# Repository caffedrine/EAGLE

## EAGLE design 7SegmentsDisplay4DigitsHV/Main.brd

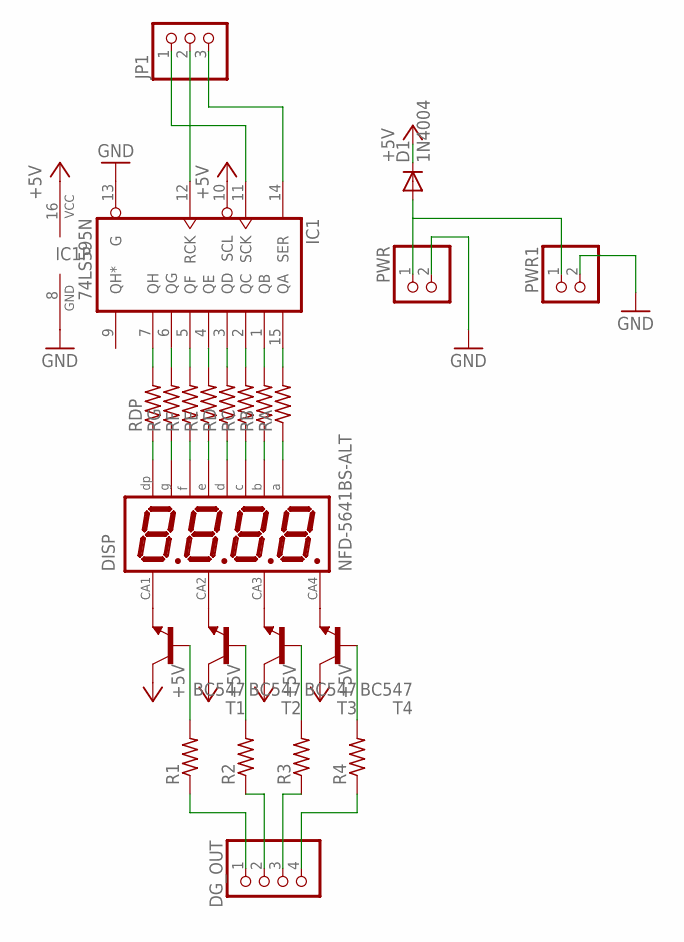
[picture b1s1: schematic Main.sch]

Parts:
D1: 1N4004; DO41-10
DG_OUT: PINHD-1X4; 1X04
DISP: NFD-5641BS-ALT; NFD-5641
IC1: 74LS595N; DIL16
JP1: PINHD-1X3; 1X03
PWR, PWR1: PINHD-1X2; 1X02
R1, R2, R3, R4: R-US_0309/12; 0309/12
RA: R-US_0309/12; 0309/12
RB: R-US_0309/12; 0309/12
RC: R-US_0309/12; 0309/12
RD: R-US_0309/12; 0309/12
RDP: R-US_0309/12; 0309/12
RE: R-US_0309/12; 0309/12
RF: R-US_0309/12; 0309/12
RG: R-US_0309/12; 0309/12
T1, T2, T3, T4: BC547; TO92

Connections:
+5V: D1.C, IC1.10 (SCL), IC1.16 (VCC), T1.3 (C), T2.3 (C), T3.3 (C), T4.3 (C)
GND: IC1.8 (GND), IC1.13 (G), PWR.2, PWR1.2
unnamed: DISP.P$12, T1.1 (E)
unnamed: DISP.P$9, T2.1 (E)
unnamed: DISP.P$8, T3.1 (E)
unnamed: DISP.P$6, T4.1 (E)
unnamed: R1.2, T1.2 (B)
unnamed: R2.2, T2.2 (B)
unnamed: R3.2, T3.2 (B)
unnamed: R4.2, T4.2 (B)
unnamed: DG_OUT.2, R2.1
unnamed: DG_OUT.3, R3.1
unnamed: DG_OUT.4, R4.1
unnamed: DG_OUT.1, R1.1
unnamed: IC1.7 (QH), RDP.2
unnamed: IC1.6 (QG), RG.2
unnamed: IC1.5 (QF), RF.2
unnamed: IC1.4 (QE), RE.2
unnamed: IC1.3 (QD), RD.2
unnamed: IC1.2 (QC), RC.2
unnamed: IC1.1 (QB), RB.2
unnamed: IC1.15 (QA), RA.2
unnamed: IC1.11 (SCK), JP1.1
unnamed: IC1.12 (RCK), JP1.2
unnamed: IC1.14 (SER), JP1.3
unnamed: DISP.P$3, RDP.1
unnamed: DISP.P$5, RG.1
unnamed: DISP.P$10, RF.1
unnamed: DISP.P$1, RE.1
unnamed: DISP.P$2, RD.1
unnamed: DISP.P$4, RC.1
unnamed: DISP.P$7, RB.1
unnamed: DISP.P$11, RA.1
unnamed: D1.A, PWR.1, PWR1.1

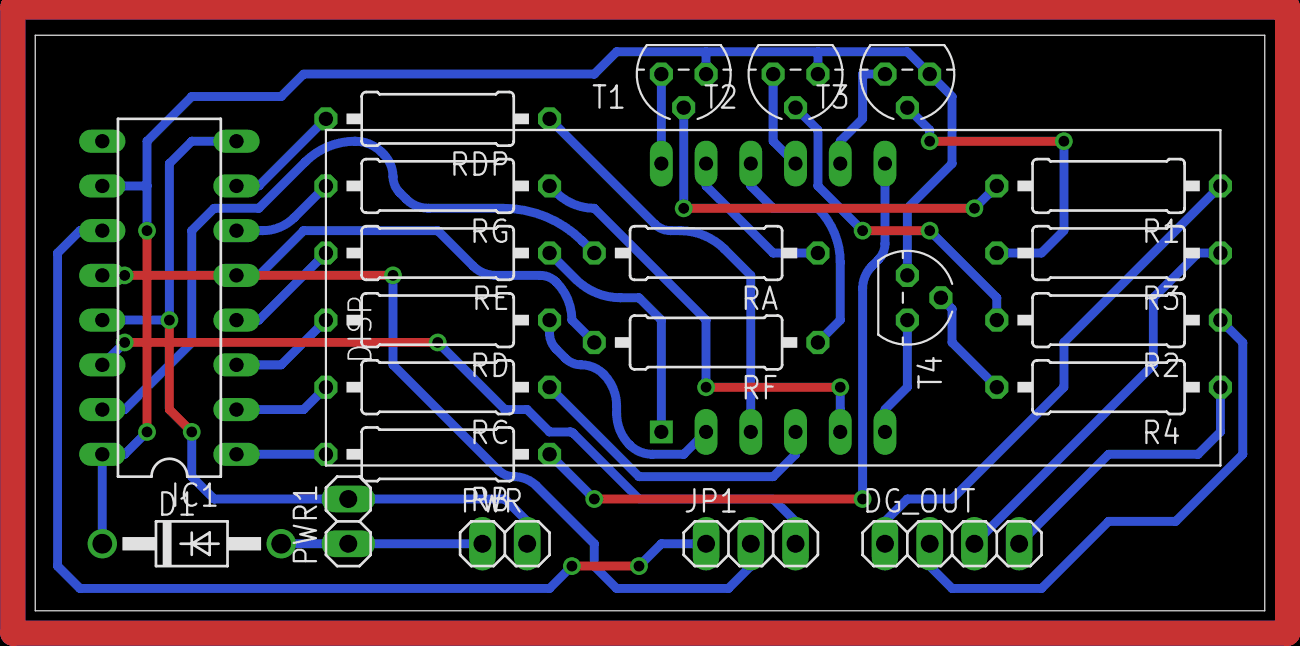
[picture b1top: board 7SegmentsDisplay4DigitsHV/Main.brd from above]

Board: 3 copper layers, 69.8 x 32.7 mm, 23 parts (0 on the bottom side), 34 nets.

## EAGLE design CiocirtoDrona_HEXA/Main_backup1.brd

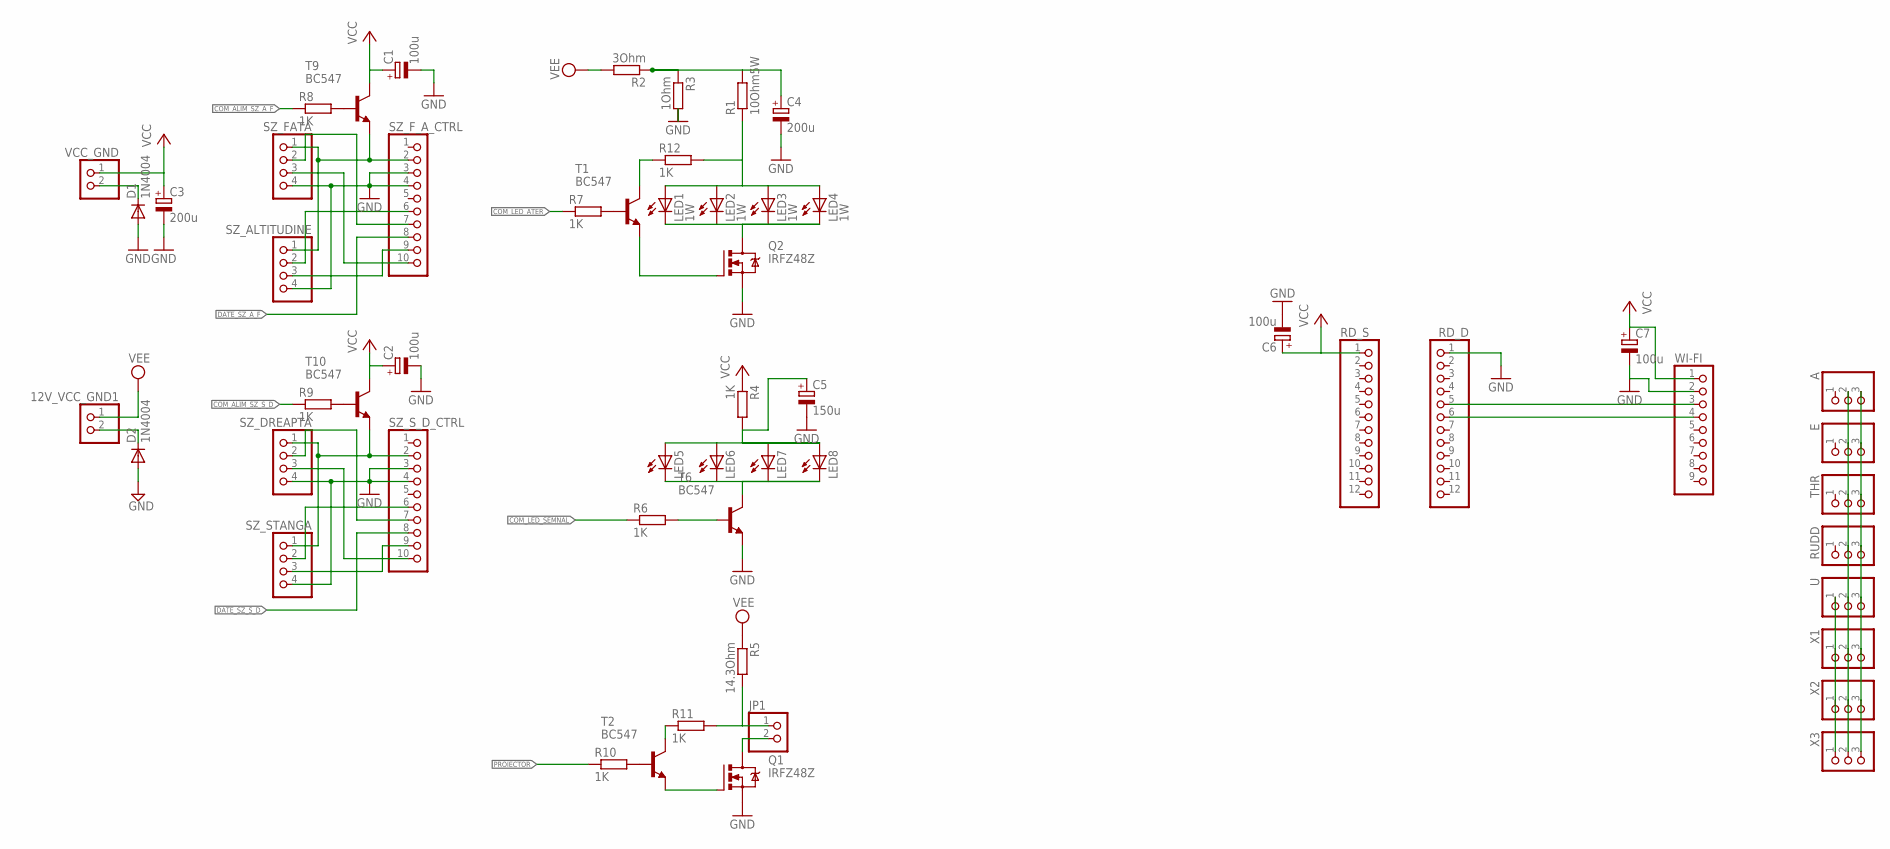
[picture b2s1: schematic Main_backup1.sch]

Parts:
12V_VCC_GND1: PINHD-1X2; 1X02
A: PINHD-1X3/90; 1X03/90
C1, C2, C6, C7: 100u; E2-5
C3, C4: 200u; E2-5
C5: 150u; E2-5
D1, D2: 1N4004; DO41-10
E: PINHD-1X3/90; 1X03/90
JP1: PINHD-1X2; 1X02
LED1, LED2, LED3, LED4: 1W; OSRAM-SIDELED
LED5, LED6, LED7, LED8: LED5MM
Q1, Q2: IRFZ48Z; TO220BH
R1: 10Ohm5W; 0309/12
R2: 3Ohm; 0309/12
R3: 1Ohm; 0309/12
R4, R6, R7, R8, R9, R10, R11, R12: 1K; 0309/12
R5: 14.3Ohm; 0309/12
RD_D: PINHD-1X12; 1X12
RD_S: PINHD-1X12; 1X12
RUDD: PINHD-1X3/90; 1X03/90
SZ_ALTITUDINE: PINHD-1X4; 1X04
SZ_DREAPTA: PINHD-1X4; 1X04
SZ_FATA: PINHD-1X4; 1X04
SZ_F_A_CTRL: PINHD-1X10; 1X10
SZ_STANGA: PINHD-1X4; 1X04
SZ_S_D_CTRL: PINHD-1X10; 1X10
T1, T2, T6, T9, T10: BC547; TO92
THR: PINHD-1X3/90; 1X03/90
U: PINHD-1X3/90; 1X03/90
VCC_GND: PINHD-1X2; 1X02
WI-FI: PINHD-1X9; 1X09
X1, X2, X3: PINHD-1X3/90; 1X03/90

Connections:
COM_ALIM_SZ_A_F: R8.1
COM_ALIM_SZ_S_D: R9.1
COM_LED_ATER: R7.1
COM_LED_SEMNAL: R6.1
DATE_SZ_A_F: SZ_F_A_CTRL.8
DATE_SZ_S_D: SZ_S_D_CTRL.8
GND: C1.-, C2.-, C3.-, C4.-, C5.-, C6.-, C7.-, D1.A, D2.A, Q1.S, Q2.S, R3.2, RD_D.1, SZ_ALTITUDINE.4, SZ_DREAPTA.4, SZ_FATA.4, SZ_F_A_CTRL.3, SZ_F_A_CTRL.4, SZ_STANGA.4, SZ_S_D_CTRL.3, SZ_S_D_CTRL.4, T6.1 (E), WI-FI.2
unnamed: SZ_FATA.2, SZ_F_A_CTRL.7
unnamed: D1.C, VCC_GND.2
unnamed: JP1.1, R5.2, R11.2
unnamed: SZ_FATA.3, SZ_F_A_CTRL.10
unnamed: SZ_ALTITUDINE.2, SZ_F_A_CTRL.6
unnamed: SZ_ALTITUDINE.3, SZ_F_A_CTRL.9
unnamed: SZ_DREAPTA.2, SZ_S_D_CTRL.7
unnamed: SZ_DREAPTA.3, SZ_S_D_CTRL.10
unnamed: SZ_STANGA.2, SZ_S_D_CTRL.6
unnamed: SZ_STANGA.3, SZ_S_D_CTRL.9
unnamed: SZ_ALTITUDINE.1, SZ_FATA.1, SZ_F_A_CTRL.2, T9.1 (E)
unnamed: SZ_DREAPTA.1, SZ_STANGA.1, SZ_S_D_CTRL.2, T10.1 (E)
unnamed: LED1.C, LED2.C, LED3.C, LED4.C, Q2.D
unnamed: LED1.A, LED2.A, LED3.A, LED4.A, R1.1, R12.2
unnamed: Q2.G, T1.1 (E)
unnamed: C4.+, R1.2, R2.1, R3.1
unnamed: 12V_VCC_GND1.2, D2.C
unnamed: LED5.K (C), LED6.K (C), LED7.K (C), LED8.K (C), T6.3 (C)
unnamed: C5.+, LED5.A, LED6.A, LED7.A, LED8.A, R4.2
unnamed: JP1.2, Q1.D
unnamed: R6.2, T6.2 (B)
unnamed: R7.2, T1.2 (B)
unnamed: R8.2, T9.2 (B)
unnamed: R9.2, T10.2 (B)
unnamed: R10.2, T2.2 (B)
unnamed: R12.1, T1.3 (C)
unnamed: R11.1, T2.3 (C)
unnamed: Q1.G, T2.1 (E)
unnamed: U.1, X1.1, X2.1, X3.1
unnamed: RD_D.5, WI-FI.3
unnamed: RD_D.6, WI-FI.4
unnamed: A.3, E.3, RUDD.3, THR.3, U.3, X1.3, X2.3, X3.3
unnamed: A.2, E.2, RUDD.2, THR.2, U.2, X1.2, X2.2, X3.2
PROIECTOR: R10.1
VCC: C1.+, C2.+, C3.+, C6.+, C7.+, R4.1, RD_S.1, T9.3 (C), T10.3 (C), VCC_GND.1, WI-FI.1
VEE: 12V_VCC_GND1.1, R2.2, R5.1

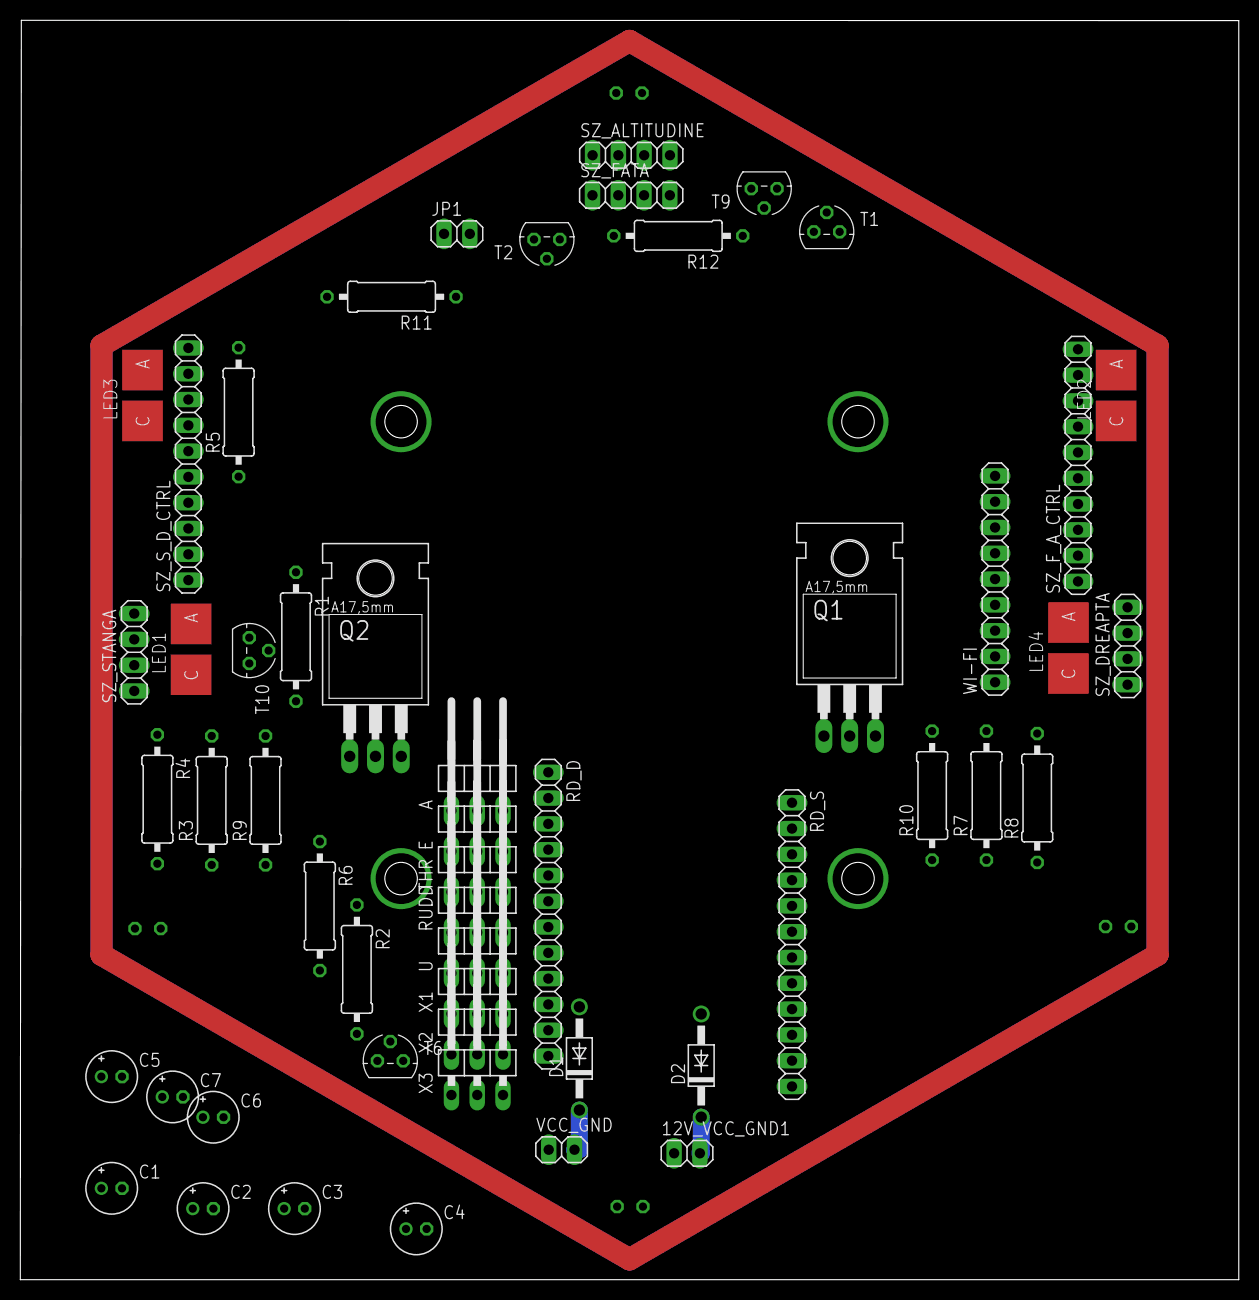
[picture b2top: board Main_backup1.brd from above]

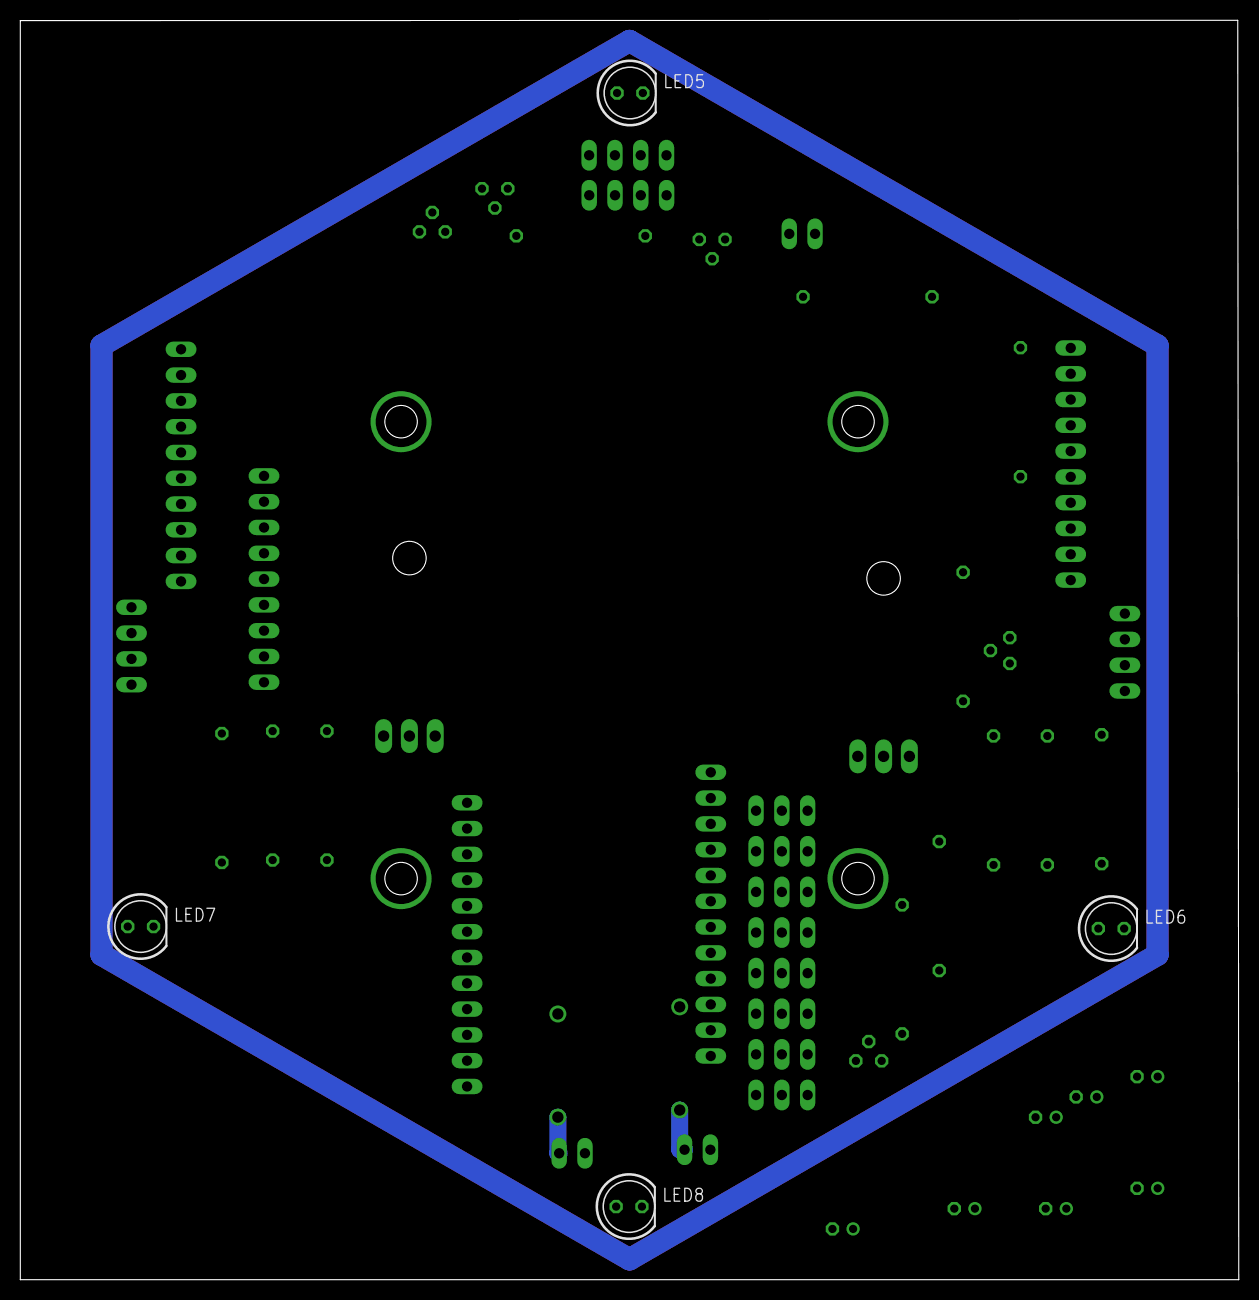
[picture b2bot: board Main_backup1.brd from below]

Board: 2 copper layers, 120.0 x 124.0 mm, 56 parts (4 on the bottom side), 36 nets.

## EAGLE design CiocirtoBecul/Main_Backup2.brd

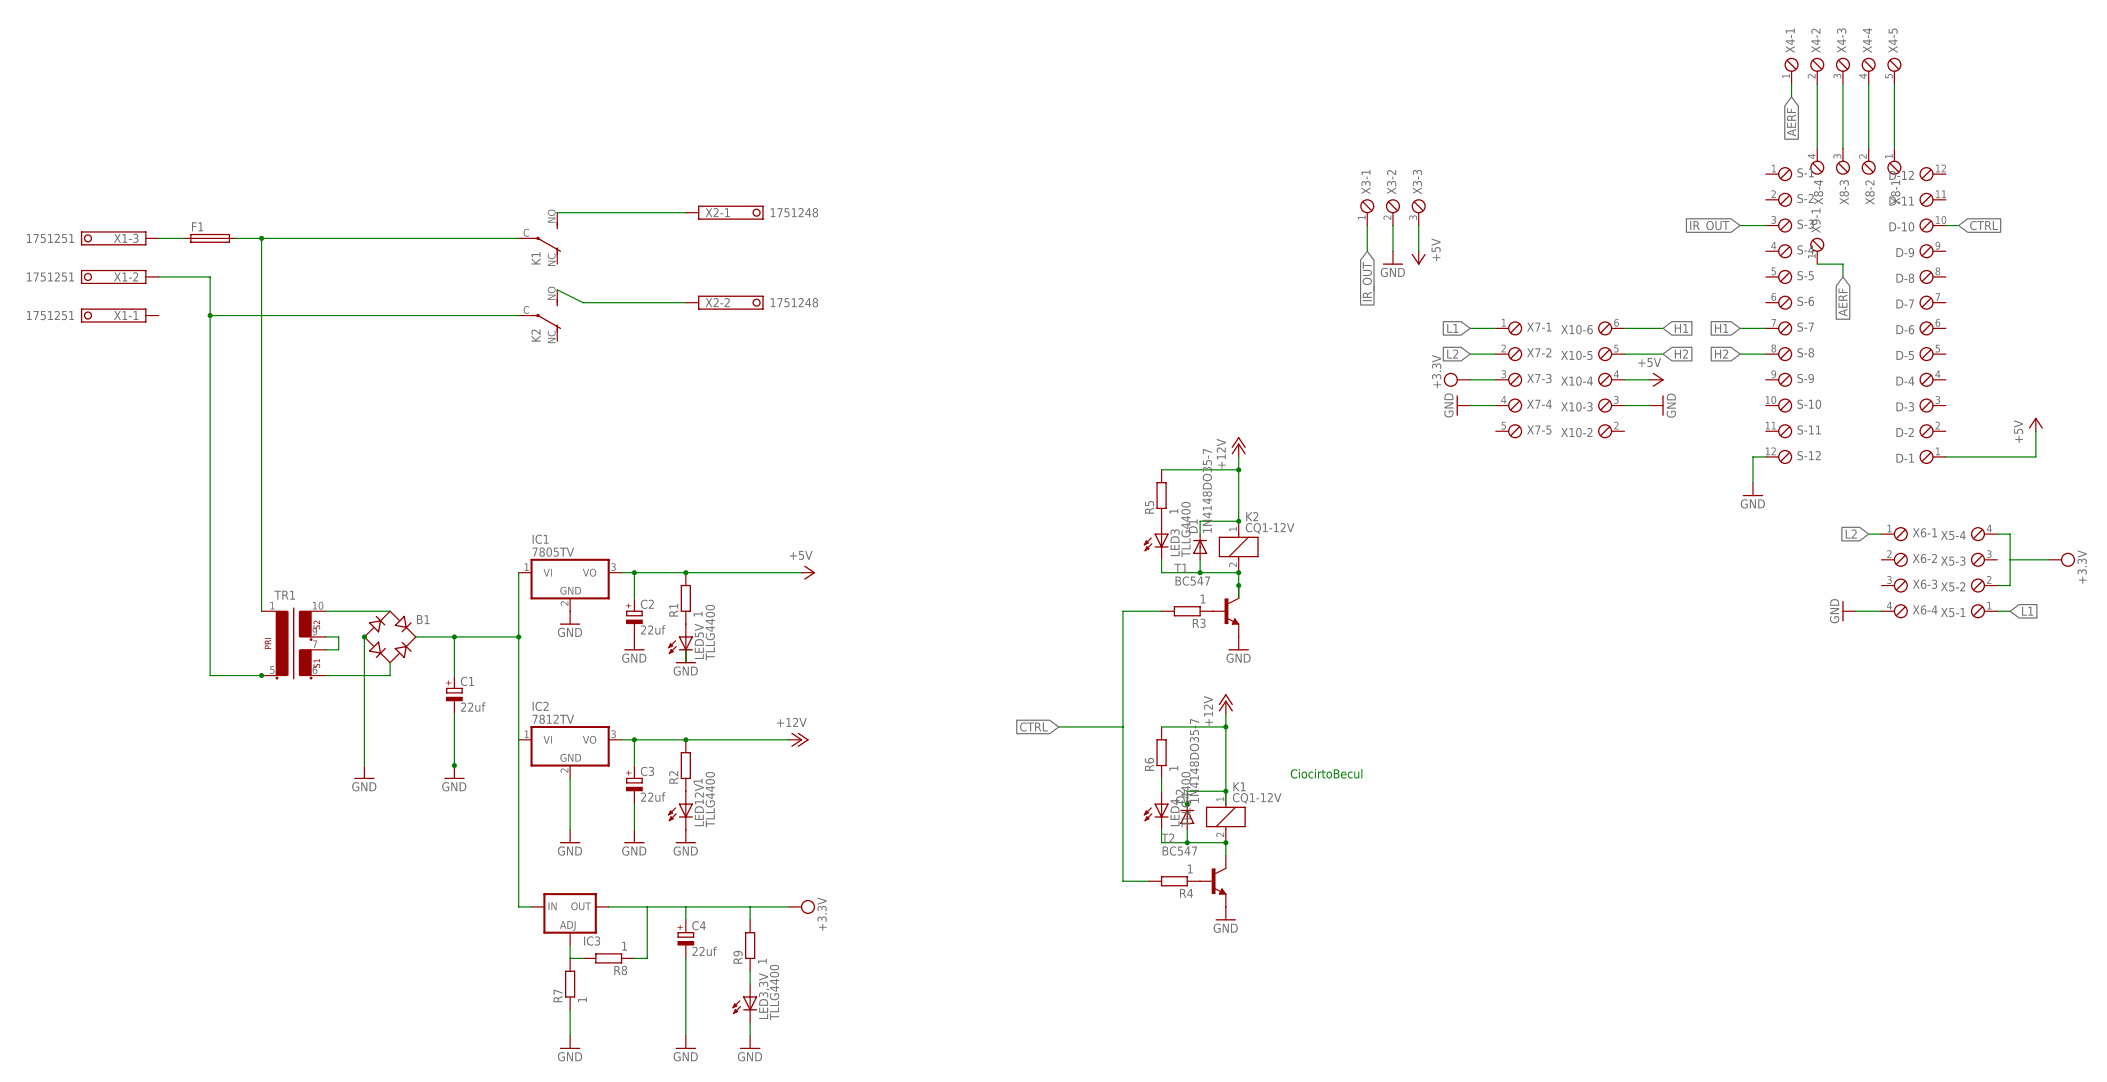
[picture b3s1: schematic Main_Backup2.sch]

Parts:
B1: RB1A
C1, C2, C3, C4: 22uf; E2-4
D: MPT12; 12POL254
D1, D2: 1N4148DO35-7; DO35-7
F1: SH25
IC1: 7805TV; TO220V
IC2: 7812TV; TO220V
IC3: LM317TS; 317TS
K1, K2: CQ1-12V; CQ1
LED3, LED3,3V, LED4, LED5V, LED12V: TLLG4400; LED3MM
R1, R2, R3, R4, R5, R6, R7, R8, R9: 1; 0204/5
S: MPT12; 12POL254
T1, T2: BC547; TO92
TR1: EI30-2
X1: 1751251
X2: 1751248
X3: MPT3; 3POL254
X4: MPT5; 5POL254
X5, X6, X8: MPT4; 4POL254
X7, X10: MPT6; 6POL254
X9: MPT2; 2POL254

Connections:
+5V: C2.+, D.1, IC1.3 (VO), R1.2, X3.3, X10.4
+12V: C3.+, D1.C, D2.C, IC2.3 (VO), K1.1, K2.1, R2.2, R5.2, R6.2
AERF: X4.1, X9.1
CTRL: D.10, R3.2, R4.2
GND: B1.-, C1.-, C2.-, C3.-, C4.-, IC1.2 (GND), IC2.2 (GND), LED3,3V.K (C), LED5V.K (C), LED12V.K (C), R7.1, S.12, T1.1 (E), T2.1 (E), X3.2, X6.4, X7.4, X10.3
H1: S.7, X10.6
H2: S.8, X10.5
IR_OUT: S.3, X3.1
L1: X5.1, X7.1
L2: X6.1, X7.2
unnamed: F1.2, K1.C, TR1.1
unnamed: K2.C, TR1.5 (2), X1.2
unnamed: K1.NO (S), X2.1
unnamed: K2.NO (S), X2.2
unnamed: TR1.7 (4), TR1.9 (5)
unnamed: B1.AC1, TR1.10 (6)
unnamed: B1.AC2, TR1.6 (3)
unnamed: B1.+, C1.+, IC1.1 (VI), IC2.1 (VI), IC3.3 (IN)
unnamed: D1.A, K2.2, LED3.K (C), T1.3 (C)
unnamed: LED12V.A, R2.1
unnamed: LED3.A, R5.1
unnamed: D2.A, K1.2, LED4.K (C), T2.3 (C)
unnamed: LED5V.A, R1.1
unnamed: R3.1, T1.2 (B)
unnamed: R4.1, T2.2 (B)
unnamed: X4.5, X8.1
unnamed: F1.1, X1.3
unnamed: LED4.A, R6.1
unnamed: IC3.1 (ADJ), R7.2, R8.2
unnamed: LED3,3V.A, R9.1
unnamed: X4.3, X8.3
unnamed: X4.4, X8.2
unnamed: X4.2, X8.4
VCC: C4.+, IC3.2 (OUT), R8.1, R9.2, X5.2, X5.4, X7.3

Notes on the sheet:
CiocirtoBecul

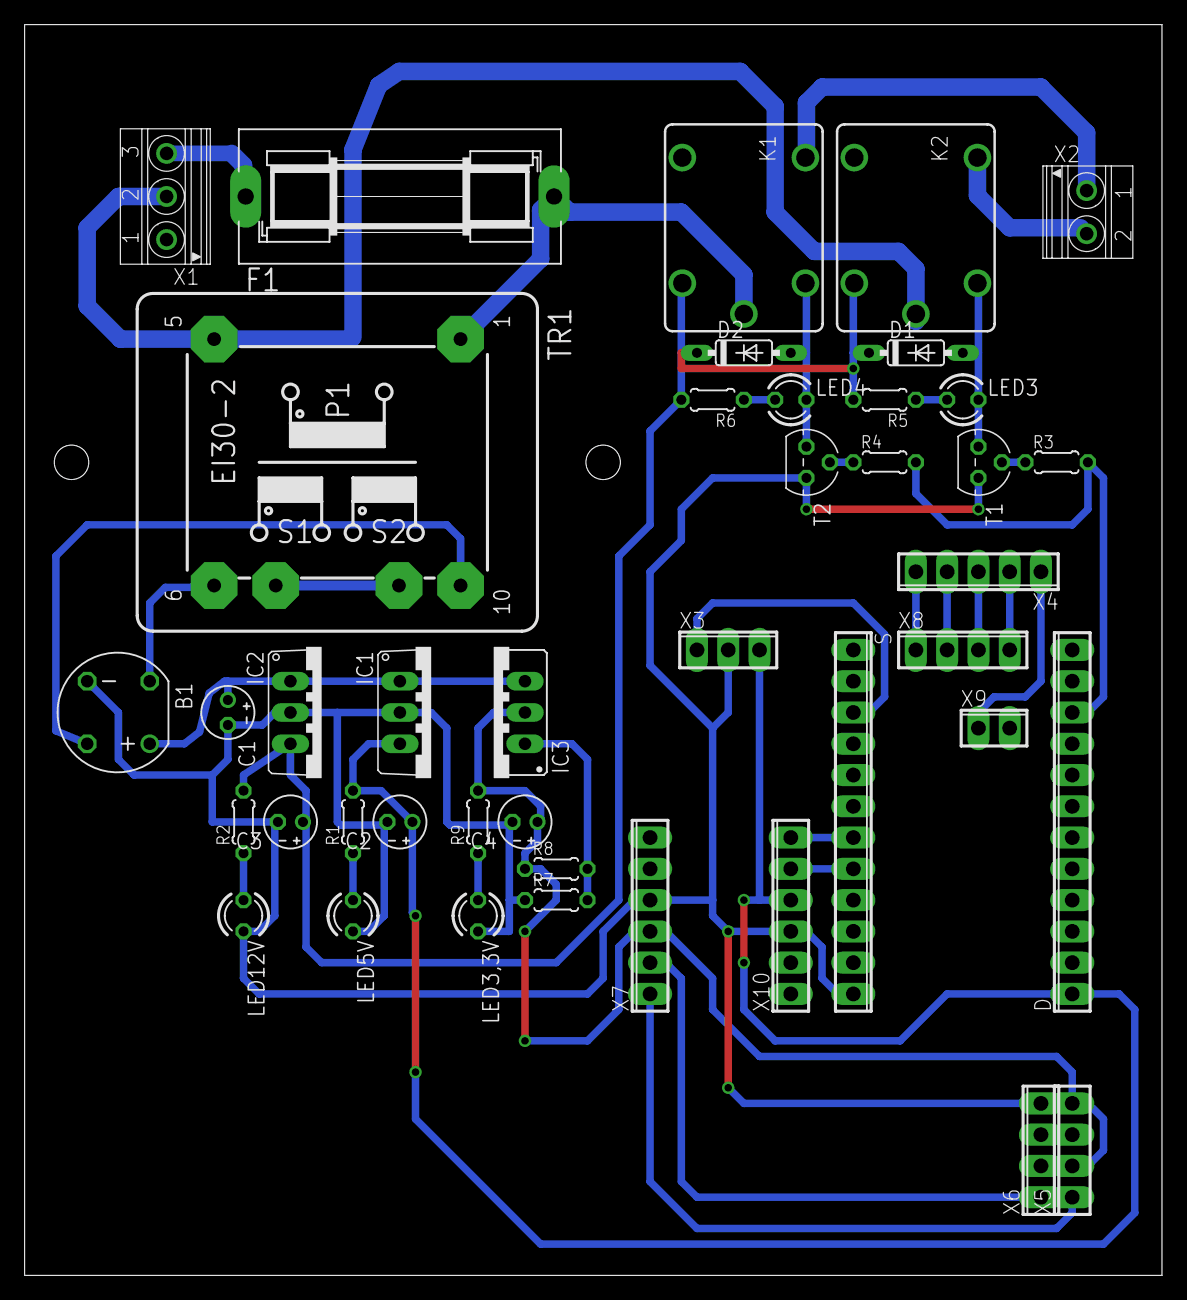
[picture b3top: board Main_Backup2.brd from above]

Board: 2 copper layers, 92.4 x 101.6 mm, 42 parts (0 on the bottom side), 34 nets.

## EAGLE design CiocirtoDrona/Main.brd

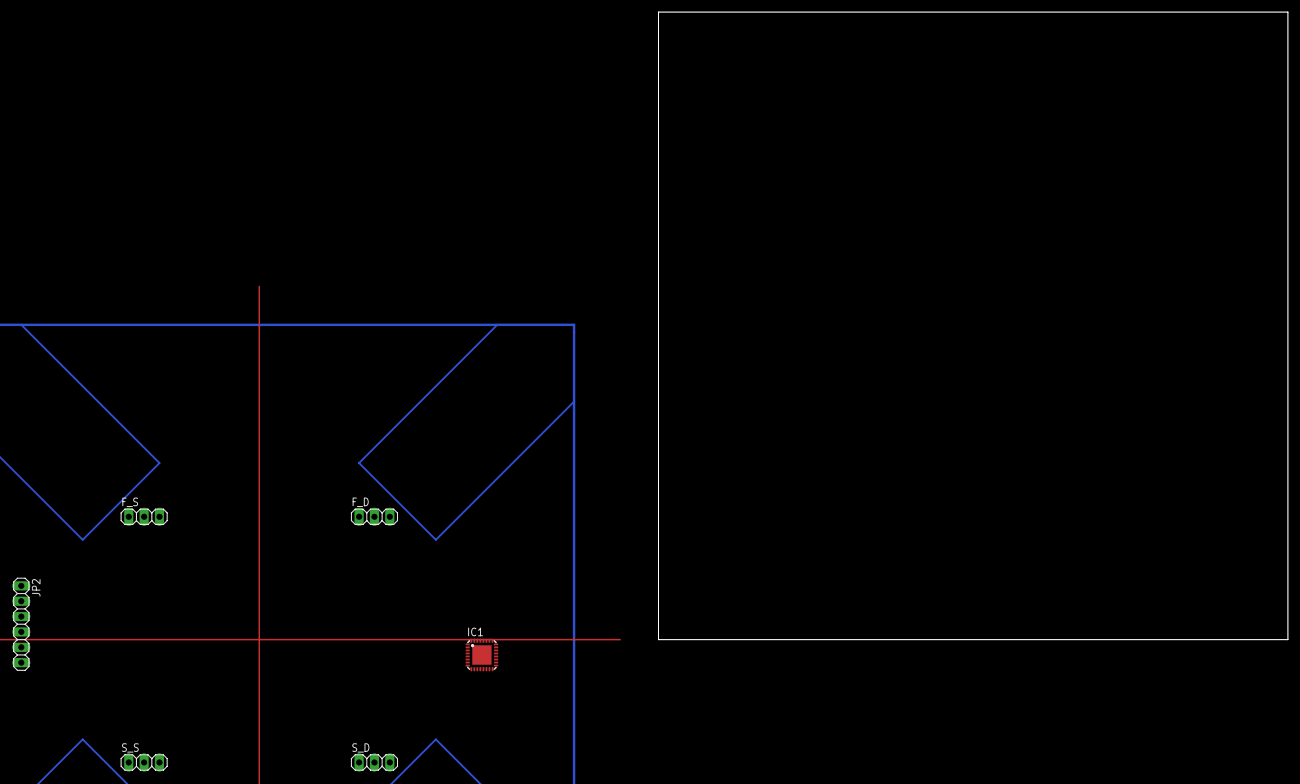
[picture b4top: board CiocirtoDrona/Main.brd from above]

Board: 2 copper layers, 104.1 x 103.8 mm, 6 parts (0 on the bottom side), 2 nets.

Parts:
F_D: 1X03
F_S: 1X03
IC1: MEGA8-MI; MLF32-TH
JP2: 1X06
S_D: 1X03
S_S: 1X03

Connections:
GND: IC1.3, IC1.5, IC1.21
VCC: IC1.4, IC1.6

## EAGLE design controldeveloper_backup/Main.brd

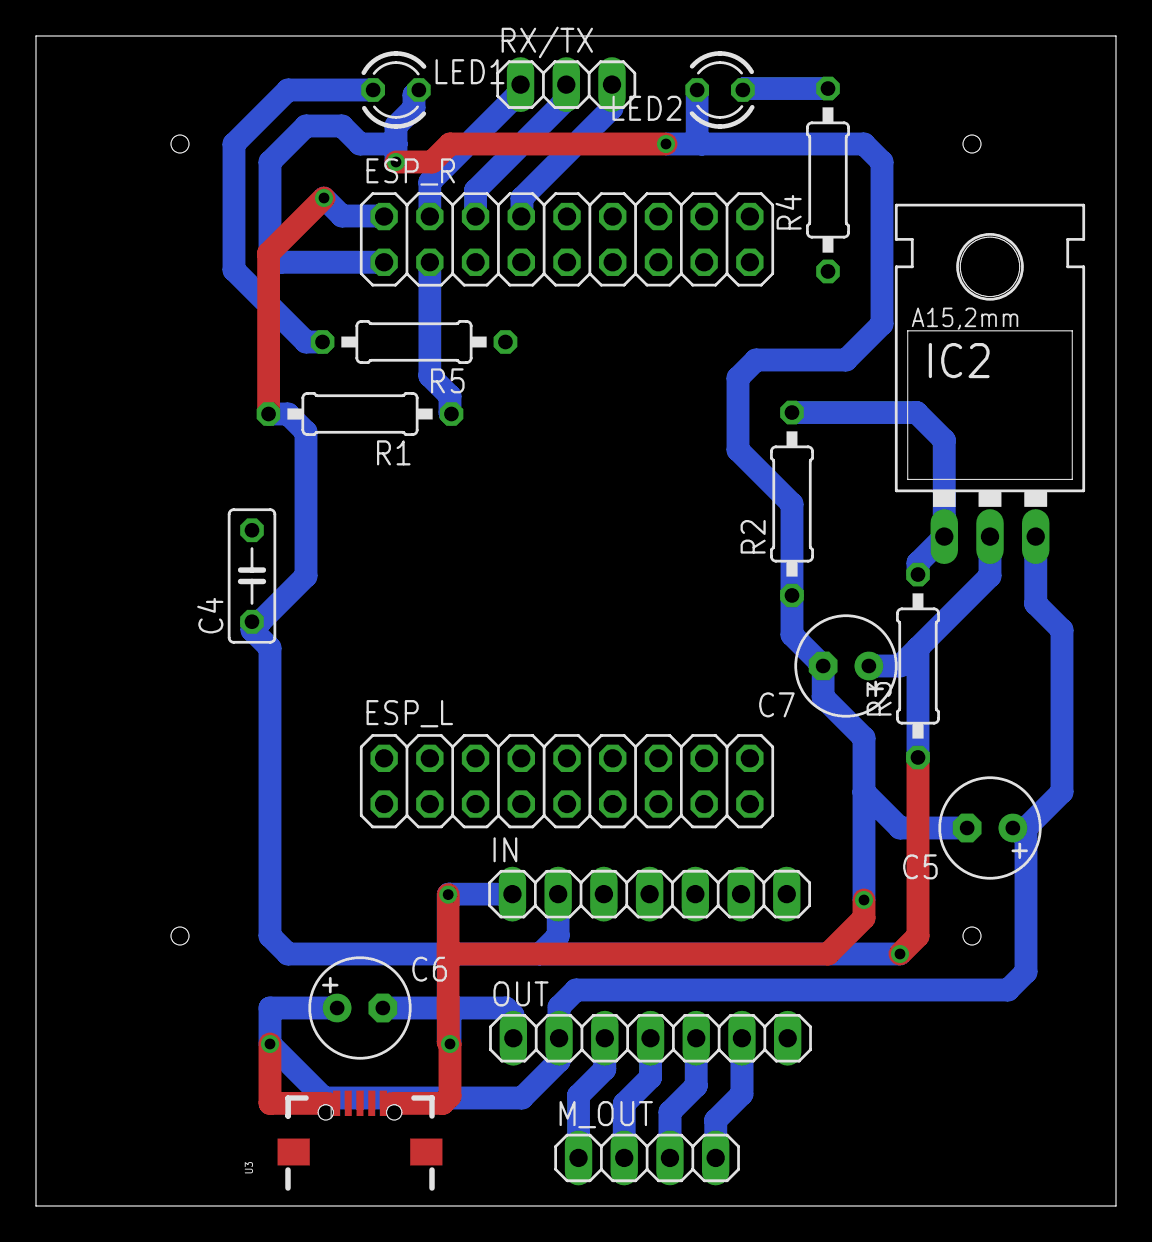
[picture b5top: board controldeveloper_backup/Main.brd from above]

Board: 2 copper layers, 60.0 x 65.0 mm, 19 parts (0 on the bottom side), 16 nets.

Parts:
C4: 10uF; C050-025X075
C5: 100uF; E2,5-6
C6: 220uF; E2,5-6
C7: 400uF; E2,5-6
ESP_L: 2X09
ESP_R: 2X09
IC2: 317TL
IN: 1X07
LED1, LED2: TLLG4400; LED3MM
M_OUT: 1X04
OUT: 1X07
R1: 12k; 0207/10
R2: 390; 0207/10
R3: 240; 0207/10
R4, R5: 10k; 0207/10
RX/TX: 1X03
U3: USB-MICRO-SMD

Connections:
EN1: ESP_L.8, IN.3
EN2: ESP_L.10, IN.5
LED1: ESP_R.9, R5.1
LED2: ESP_R.11, R4.1
unnamed: M_OUT.1, OUT.3
unnamed: M_OUT.2, OUT.4
unnamed: M_OUT.3, OUT.5
unnamed: M_OUT.4, OUT.6
unnamed: IC2.1, R2.2, R3.2
unnamed: LED2.A, R4.2
unnamed: C4.2, C5.-, C6.-, C7.-, ESP_R.1, ESP_R.3, ESP_R.5, IN.1, LED1.K, LED2.K, OUT.1, R1.1, R2.1, U3.GND1
unnamed: LED1.A, R5.2
PH1: ESP_L.9, IN.4
PH2: ESP_L.7, IN.6
VCC: C4.1, C7.+, ESP_R.2, ESP_R.4, ESP_R.6, ESP_R.8, ESP_R.10, IC2.2, IN.2, R1.2, R3.1, RX/TX.1, RX/TX.2, RX/TX.3
VDD: C5.+, C6.+, IC2.3, OUT.2, U3.VBUS1

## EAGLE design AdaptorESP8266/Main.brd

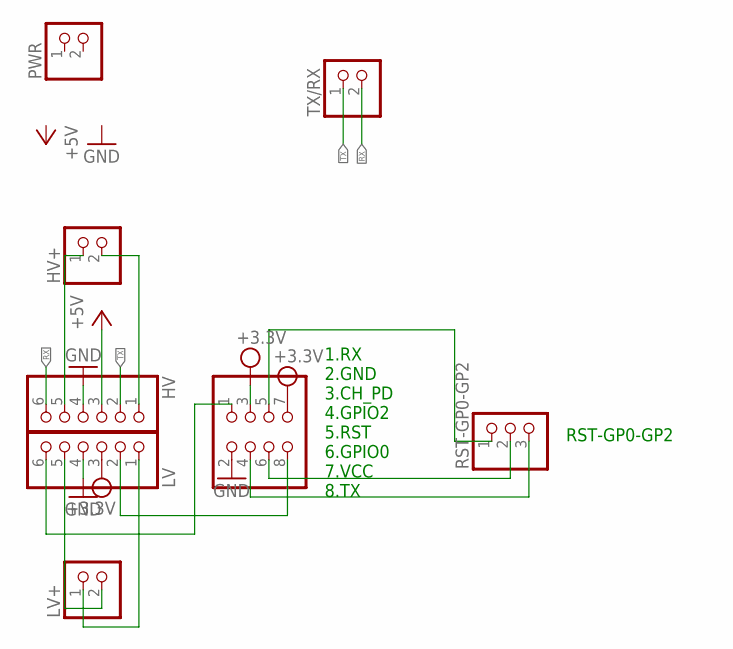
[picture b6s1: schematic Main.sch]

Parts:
HV: PINHD-1X6; 1X06
HV+: PINHD-1X2; 1X02
LV: PINHD-1X6; 1X06
LV+: PINHD-1X2; 1X02
PWR: PINHD-1X2; 1X02
RST-GP0-GP2: PINHD-1X3; 1X03
SOCLU_ESP: PINHD-2X4; 2X04
TX/RX: PINHD-1X2; 1X02

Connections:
GND: HV.4, LV.4, SOCLU_ESP.2
unnamed: LV.2, SOCLU_ESP.8
unnamed: RST-GP0-GP2.1, SOCLU_ESP.5
unnamed: RST-GP0-GP2.2, SOCLU_ESP.6
unnamed: LV.6, SOCLU_ESP.1
unnamed: RST-GP0-GP2.3, SOCLU_ESP.4
unnamed: HV.5, HV+.1
unnamed: HV.1, HV+.2
unnamed: LV.1, LV+.1
unnamed: LV.5, LV+.2
RX: HV.6, TX/RX.2
TX: HV.2, TX/RX.1
VCC: HV.3
VDD: LV.3, SOCLU_ESP.3, SOCLU_ESP.7

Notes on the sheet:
1.RX 2.GND 3.CH_PD 4.GPIO2 5.RST 6.GPIO0 7.VCC 8.TX
RST-GP0-GP2

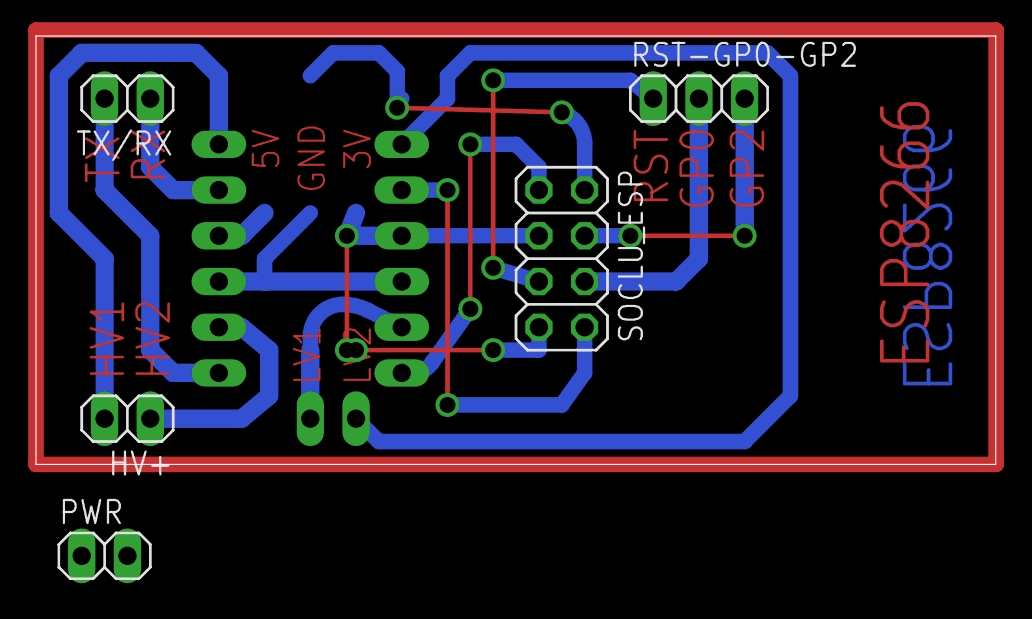
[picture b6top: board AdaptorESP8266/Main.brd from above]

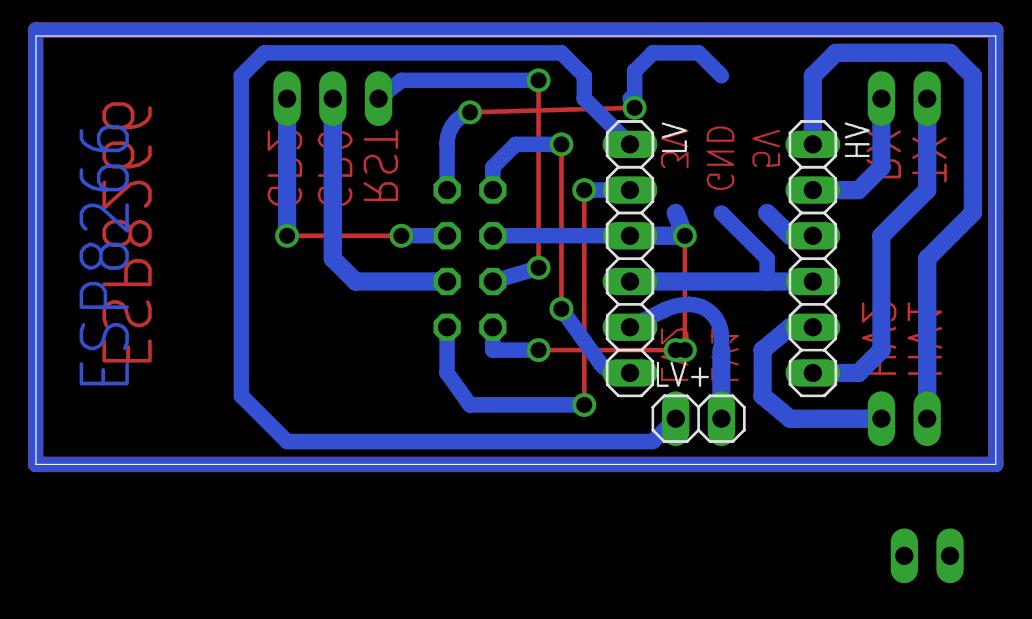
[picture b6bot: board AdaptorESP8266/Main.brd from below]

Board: 2 copper layers, 53.3 x 23.8 mm, 8 parts (3 on the bottom side), 13 nets.

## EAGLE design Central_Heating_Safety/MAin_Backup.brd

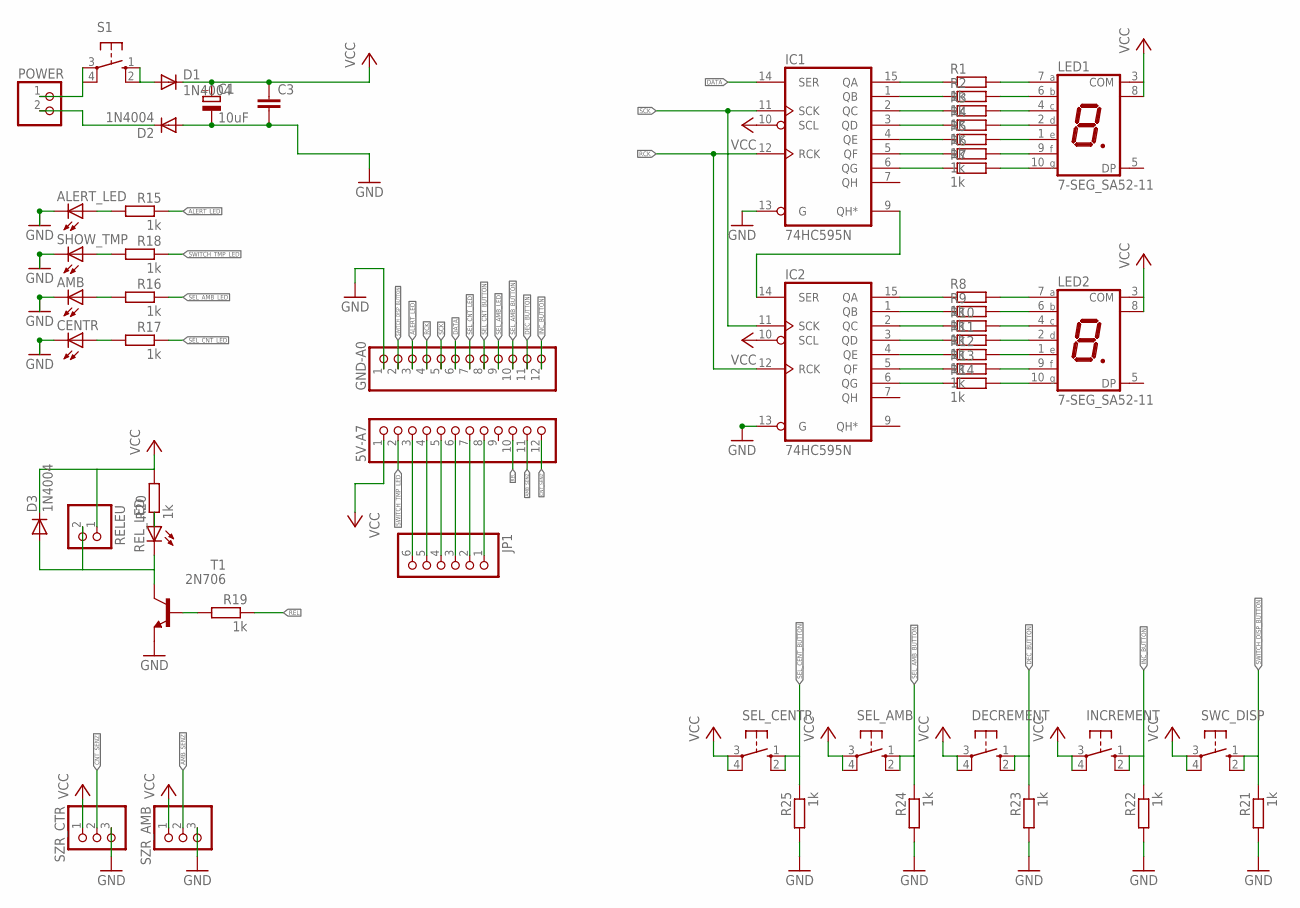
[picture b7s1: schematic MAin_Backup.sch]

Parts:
5V-A7: PINHD-1X12; 1X12
ALERT_LED: LED5MM
AMB: LED5MM
C1: 10uF; E2-5
C3: C-EU025-024X044; C025-024X044
CENTR: LED5MM
D1, D2, D3: 1N4004; DO41-10
DECREMENT: 40-XX; B3F-40XX
GND-A0: PINHD-1X12; 1X12
IC1, IC2: 74HC595N; DIL16
INCREMENT: 40-XX; B3F-40XX
JP1: PINHD-1X6; 1X06
LED1, LED2: 7-SEG_SA52-11; SA52-11
POWER: PINHD-1X2; 1X02
R1, R2, R3, R4, R5, R6, R7, R8, R9, R10, R11, R12, R13, R14, R15, R16, R17, R18, R19, R20, R21, R22, R23, R24, R25: 1k; 0309/12
RELEU: PINHD-1X2; 1X02
REL_LED: LED5MM
S1: 10-XX; B3F-10XX
SEL_AMB: 40-XX; B3F-40XX
SEL_CENTR: 40-XX; B3F-40XX
SHOW_TMP: LED5MM
SWC_DISP: 40-XX; B3F-40XX
SZR_AMB: PINHD-1X3; 1X03
SZR_CTR: PINHD-1X3; 1X03
T1: 2N706; TO18

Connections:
ALERT_LED: GND-A0.3, R15.1
AMB_SENZ: 5V-A7.11, SZR_AMB.2
CNT_SENZ: 5V-A7.12, SZR_CTR.2
DATA: GND-A0.6, IC1.14 (SER)
DEC_BUTTON: DECREMENT.1 (S), DECREMENT.2 (S1), GND-A0.11, R23.1
GND: ALERT_LED.K (C), AMB.K (C), C1.-, C3.2, CENTR.K (C), D2.A, GND-A0.1, IC1.8 (GND), IC1.13 (G), IC2.8 (GND), IC2.13 (G), R21.2, R22.2, R23.2, R24.2, R25.2, SHOW_TMP.K (C), SZR_AMB.3, SZR_CTR.3, T1.1 (E)
INC_BUTTON: GND-A0.12, INCREMENT.1 (S), INCREMENT.2 (S1), R22.1
unnamed: LED1.7 (A), R1.2
unnamed: LED1.6 (B), R2.2
unnamed: LED1.4 (C), R3.2
unnamed: LED1.2 (D), R4.2
unnamed: LED1.1 (E), R5.2
unnamed: LED1.9 (F), R6.2
unnamed: LED1.10 (G), R7.2
unnamed: LED2.7 (A), R8.2
unnamed: LED2.6 (B), R9.2
unnamed: LED2.4 (C), R10.2
unnamed: LED2.2 (D), R11.2
unnamed: LED2.1 (E), R12.2
unnamed: LED2.9 (F), R13.2
unnamed: LED2.10 (G), R14.2
unnamed: IC1.15 (QA), R1.1
unnamed: IC1.1 (QB), R2.1
unnamed: IC1.2 (QC), R3.1
unnamed: IC1.3 (QD), R4.1
unnamed: IC1.4 (QE), R5.1
unnamed: IC1.5 (QF), R6.1
unnamed: IC1.6 (QG), R7.1
unnamed: IC2.15 (QA), R8.1
unnamed: IC2.1 (QB), R9.1
unnamed: IC2.2 (QC), R10.1
unnamed: IC2.3 (QD), R11.1
unnamed: IC2.4 (QE), R12.1
unnamed: IC2.5 (QF), R13.1
unnamed: IC2.6 (QG), R14.1
unnamed: IC1.9 (QH*), IC2.14 (SER)
unnamed: 5V-A7.8, JP1.1
unnamed: 5V-A7.7, JP1.2
unnamed: 5V-A7.6, JP1.3
unnamed: 5V-A7.5, JP1.4
unnamed: 5V-A7.4, JP1.5
unnamed: 5V-A7.3, JP1.6
unnamed: D1.A, S1.1 (S), S1.2 (S1)
unnamed: POWER.1, S1.3, S1.4 (P1)
unnamed: ALERT_LED.A, R15.2
unnamed: D2.C, POWER.2
unnamed: R20.1, REL_LED.A
unnamed: R19.2, T1.2 (B)
unnamed: AMB.A, R16.2
unnamed: CENTR.A, R17.2
unnamed: R18.2, SHOW_TMP.A
unnamed: D3.A, RELEU.2, REL_LED.K (C), T1.3 (C)
RCK: GND-A0.4, IC1.12 (RCK), IC2.12 (RCK)
REL: 5V-A7.10, R19.1
SCK: GND-A0.5, IC1.11 (SCK), IC2.11 (SCK)
SEL_AMB_BUTTON: GND-A0.10, R24.1, SEL_AMB.1 (S), SEL_AMB.2 (S1)
SEL_AMB_LED: GND-A0.9, R16.1
SEL_CENT_BUTTON: GND-A0.7, R25.1, SEL_CENTR.1 (S), SEL_CENTR.2 (S1)
SEL_CNT_BUTTON: GND-A0.8
SEL_CNT_LED: R17.1
SWITCH_DISP_BUTTON: GND-A0.2, R21.1, SWC_DISP.1 (S), SWC_DISP.2 (S1)
SWITCH_TMP_LED: 5V-A7.2, R18.1
VCC: 5V-A7.1, C1.+, C3.1, D1.C, D3.C, DECREMENT.3, DECREMENT.4 (P1), IC1.10 (SCL), IC1.16 (VCC), IC2.10 (SCL), IC2.16 (VCC), INCREMENT.3, INCREMENT.4 (P1), LED1.3 (COM), LED1.8 (COM), LED2.3 (COM), LED2.8 (COM), R20.2, RELEU.1, SEL_AMB.3, SEL_AMB.4 (P1), SEL_CENTR.3, SEL_CENTR.4 (P1), SWC_DISP.3, SWC_DISP.4 (P1), SZR_AMB.1, SZR_CTR.1
